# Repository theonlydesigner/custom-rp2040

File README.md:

# week 1: rp2040 dev board

## project goals
* **Target Specs:** custom RP2040 microcontroller board using the QFN-56 package, 16MB QSPI flash, 12MHz crystal oscillator, USB-C connector with 5.1k CC pull-down resistors and dual-row breakout headers for all GPIO pins to drive a mini hackpad.
* **Design Philosophy:** build a functional dev board from absolute ground zero using the hack club stasis guide so i finally understand what goes on under the hood of a raspberry pi pico [instead of treating microcontrollers like magic black boxes].
* **Why I'm building this:** week 1 theme is PCB and i needed a custom board to integrate with an old mini hackpad design i had lying around. also i wanted to suffer through routing 0402 passives and tiny IC pins.

## deep brief
this project is essentially a custom raspberry pi pico clone built from scratch using the hack club stasis devboard guide. instead of buying a ready-made dev board you have to manually route every single trace and place every tiny passive component [because suffering builds character]. 

at the center of the madness is the RP2040 microcontroller chip which handles all the processing. it is paired with a W25Q128 QSPI flash memory chip for storing firmware and a 12MHz crystal oscillator to provide the clock signal. power is delivered via a USB-C connector featuring 5.1k pull-down resistors so modern power supplies actually negotiate power correctly. an MCP1700 LDO voltage regulator takes that input and steps it down to a stable 3.3V for the system. finally every single GPIO pin is broken out onto dual headers so the board can easily interface with a mini hackpad.

## bill of materials (BOM)

| Part | Quantity | No of items in 1 unit | Price w/o shipping | Price |
| :--- | :---: | :---: | :---: | :---: |
| 1uF Capacitor | 1 | 2 | 0.1 | 0.1 |
| 0.1uF Capacitor | 1 | 11 | 0.1 | 0.1 |
| 10uF Capacitor | 1 | 2 | 0.1 | 0.1 |
| 33pF Capacitor | 1 | 2 | 0.2 | 0.2 |
| USB_C_Receptacle_USB2.0_14P | 1 | 1 | 0.3 | 0.3 |
| Conn_01x20 | 1 | 2 | 0.6 | 0.6 |
| Conn_01x03 | 1 | 1 | 0.16 | 0.16 |
| 5.1K Resistor | 1 | 2 | 0.1 | 0.1 |
| 27 Resistor | 1 | 2 | 0.1 | 0.1 |
| 1K Resistor | 1 | 2 | 0.1 | 0.1 |
| 10K Resistor | 1 | 1 | 0.1 | 0.1 |
| SW_Push | 1 | 1 | 0.11 | 0.11 |
| RP2040 Chip | 1 | 1 | 0.84 | 1.3 |
| MCP1700x-330xxTT | 1 | 1 | 0.5 | 0.5 |
| W25Q128JVS | 1 | 1 | 5.02 | 5.02 |
| 12MHz Crystal | 1 | 1 | 0.39 | 0.39 |
| PCB w/ Stencil | 1 | 1 | 6 | 10 |
| Solder Paste | 1 | 1 | 2.3 | 3 |
| Tweezers | 1 | 1 | 1.8 | 1.8 |
| Solder Iron and stuff related to that | 1 | 1 | 3.2 | 3.2 |

## visual showcase

*(a gorgeous 3D render of a board that will probably release the magic smoke the second power is applied)*

*(the schematic page where i stared into the void until the net names started making sense)*

*(the actual PCB layout before sending it off to the fab house to be judged)*

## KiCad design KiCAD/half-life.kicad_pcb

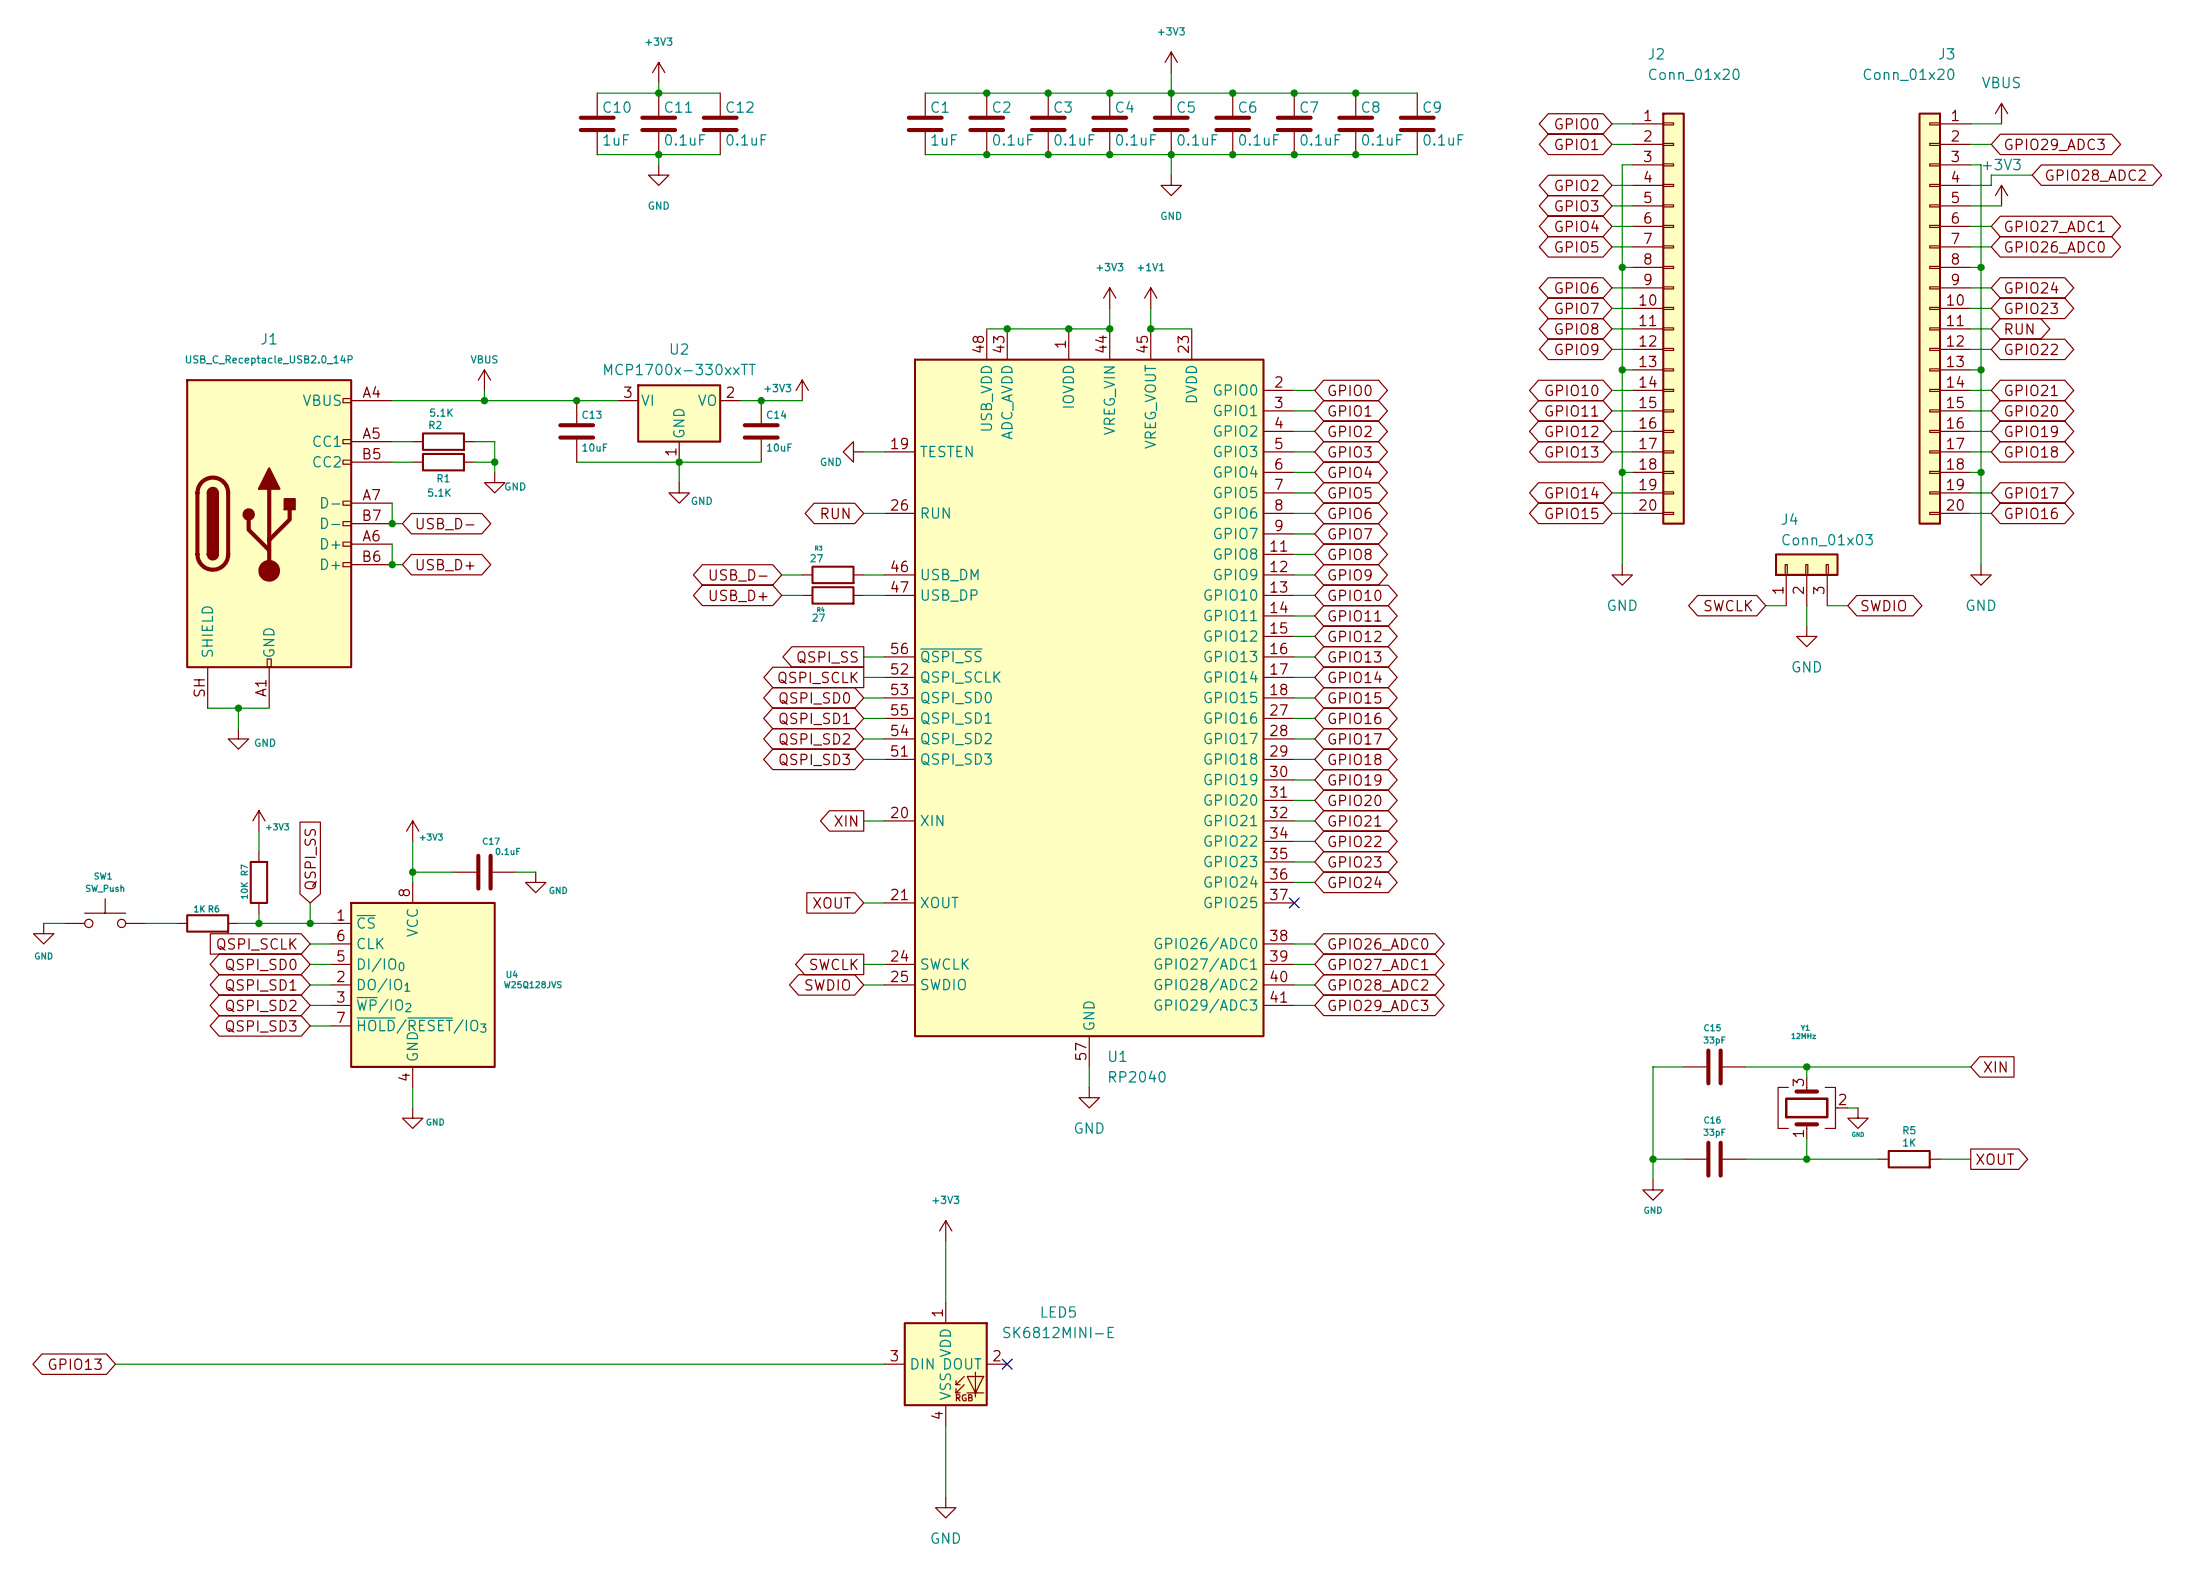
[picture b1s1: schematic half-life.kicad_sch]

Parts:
C1, C10: 1uF; C_0402_1005Metric
C2, C3, C4, C5, C6, C7, C8, C9, C11, C12, C17: 0.1uF; C_0402_1005Metric
C13, C14: 10uF; C_0603_1608Metric
C15, C16: 33pF; C_0603_1608Metric
J1: USB_C_Receptacle_USB2.0_14P; USB_C_Receptacle_HRO_TYPE-C-31-M-12
J2, J3: Conn_01x20; PinHeader_1x20_P2.54mm_Vertical
J4: Conn_01x03; PinHeader_1x03_P2.54mm_Vertical
LED5: SK6812MINI-E; LED_SK6812MINI-E_3.2x2.8mm_P1.5mm_ReverseMount
R1, R2: 5.1K; R_0402_1005Metric
R3, R4: 27; R_0402_1005Metric
R5, R6: 1K; R_0402_1005Metric
R7: 10K; R_0402_1005Metric
SW1: SW_Push; SW_Push_SPST_NO_Alps_SKRK
U1: RP2040; QFN-56-1EP_7x7mm_P0.4mm_EP3.2x3.2mm
U2: MCP1700x-330xxTT; SOT-23
U4: W25Q128JVS; Winbond_USON-8-1EP_3x2mm_P0.5mm_EP0.2x1.6mm
Y1: 12MHz; Crystal_SMD_3225-4Pin_3.2x2.5mm

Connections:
+1V1: U1.23 (DVDD), U1.45 (VREG_VOUT), U1.50 (DVDD)
+3V3: C1.1, C2.1, C3.1, C4.1, C5.1, C6.1, C7.1, C8.1, C9.1, C10.1, C11.1, C12.1, C14.1, C17.1, J3.5, LED5.1 (VDD), R7.2, U1.1 (IOVDD), U1.10 (IOVDD), U1.22 (IOVDD), U1.33 (IOVDD), U1.42 (IOVDD), U1.43 (ADC_AVDD), U1.44 (VREG_VIN), U1.48 (USB_VDD), U1.49 (IOVDD), U2.2 (VO), U4.8 (VCC)
GND: C1.2, C2.2, C3.2, C4.2, C5.2, C6.2, C7.2, C8.2, C9.2, C10.2, C11.2, C12.2, C13.2, C14.2, C15.1, C16.1, C17.2, J1.A1 (GND), J1.A12 (GND), J1.B1 (GND), J1.B12 (GND), J1.SH (SHIELD), J2.3, J2.8, J2.13, J2.18, J3.3, J3.8, J3.13, J3.18, J4.2, LED5.4 (VSS), R1.2, R2.2, SW1.1, U1.19 (TESTEN), U1.57 (GND), U2.1 (GND), U4.4 (GND), Y1.2 (G), Y1.4 (G)
GPIO0: J2.1, U1.2 (GPIO0)
GPIO1: J2.2, U1.3 (GPIO1)
GPIO2: J2.4, U1.4 (GPIO2)
GPIO3: J2.5, U1.5 (GPIO3)
GPIO4: J2.6, U1.6 (GPIO4)
GPIO5: J2.7, U1.7 (GPIO5)
GPIO6: J2.9, U1.8 (GPIO6)
GPIO7: J2.10, U1.9 (GPIO7)
GPIO8: J2.11, U1.11 (GPIO8)
GPIO9: J2.12, U1.12 (GPIO9)
GPIO10: J2.14, U1.13 (GPIO10)
GPIO11: J2.15, U1.14 (GPIO11)
GPIO12: J2.16, U1.15 (GPIO12)
GPIO13: J2.17, LED5.3 (DIN), U1.16 (GPIO13)
GPIO14: J2.19, U1.17 (GPIO14)
GPIO15: J2.20, U1.18 (GPIO15)
GPIO16: J3.20, U1.27 (GPIO16)
GPIO17: J3.19, U1.28 (GPIO17)
GPIO18: J3.17, U1.29 (GPIO18)
GPIO19: J3.16, U1.30 (GPIO19)
GPIO20: J3.15, U1.31 (GPIO20)
GPIO21: J3.14, U1.32 (GPIO21)
GPIO22: J3.12, U1.34 (GPIO22)
GPIO23: J3.10, U1.35 (GPIO23)
GPIO24: J3.9, U1.36 (GPIO24)
GPIO26_ADC0: J3.7, U1.38 (GPIO26/ADC0)
GPIO27_ADC1: J3.6, U1.39 (GPIO27/ADC1)
GPIO28_ADC2: J3.4, U1.40 (GPIO28/ADC2)
GPIO29_ADC3: J3.2, U1.41 (GPIO29/ADC3)
unnamed: C16.2, R5.1, Y1.1
unnamed: J1.A5 (CC1), R2.1
unnamed: J1.B5 (CC2), R1.1
unnamed: R6.1, SW1.2
unnamed: R3.2, U1.46 (USB_DM)
unnamed: R4.2, U1.47 (USB_DP)
QSPI_SCLK: U1.52 (QSPI_SCLK), U4.6 (CLK)
QSPI_SD0: U1.53 (QSPI_SD0), U4.5 (DI/IO_{0})
QSPI_SD1: U1.55 (QSPI_SD1), U4.2 (DO/IO_{1})
QSPI_SD2: U1.54 (QSPI_SD2), U4.3 (~WP/IO_{2})
QSPI_SD3: U1.51 (QSPI_SD3), U4.7 (~HOLD/~RESET/IO_{3})
QSPI_SS: R6.2, R7.1, U1.56 (~QSPI_SS), U4.1 (~CS)
RUN: J3.11, U1.26 (RUN)
SWCLK: J4.1, U1.24 (SWCLK)
SWDIO: J4.3, U1.25 (SWDIO)
USB_D+: J1.A6 (D+), J1.B6 (D+), R4.1
USB_D-: J1.A7 (D-), J1.B7 (D-), R3.1
VBUS: C13.1, J1.A4 (VBUS), J1.A9 (VBUS), J1.B4 (VBUS), J1.B9 (VBUS), J3.1, U2.3 (VI)
XIN: C15.2, U1.20 (XIN), Y1.3
XOUT: R5.2, U1.21 (XOUT)

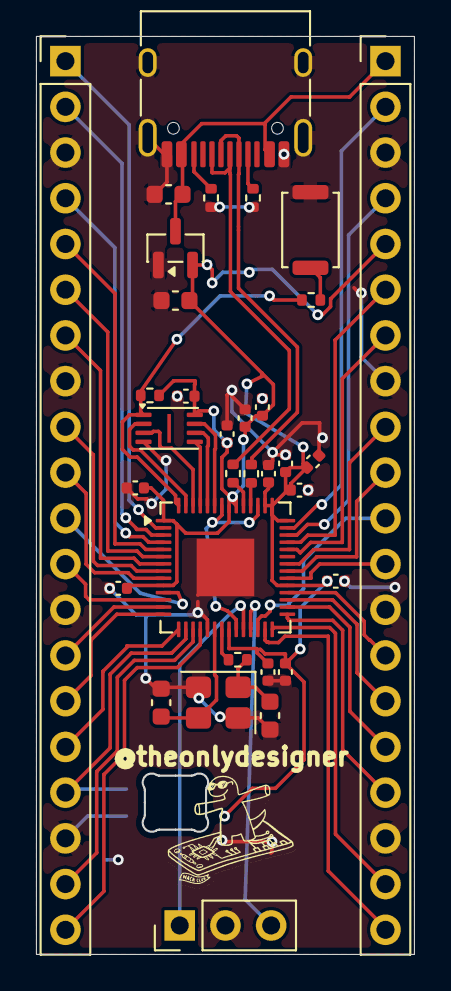
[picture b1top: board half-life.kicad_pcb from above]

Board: 2 copper layers, 21.0 x 51.0 mm, 34 parts (1 on the bottom side), 52 nets.

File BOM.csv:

Item,Qty,Supplier,Cost/item,Total Cost,link
1uF Capacitor,1,,$0.10,$0.10,
0.1uF Capacitor,1,,$0.10,$0.10,
10uF Capacitor,1,,$0.10,$0.10,
33pF Capacitor,1,,$0.20,$0.20,
USB_C_Receptacle_USB2.0_14P,1,,$0.30,$0.30,
Conn_01x20,1,,$0.60,$0.60,
Conn_01x03,1,,$0.16,$0.16,
5.1K Resistor,1,,$0.10,$0.10,
27 Resistor,1,,$0.10,$0.10,
1K Resistor,1,,$0.10,$0.10,
10K Resistor,1,,$0.10,$0.10,
SW_Push,1,,$0.11,$0.11,
RP2040 Chip,1,,$1.30,$1.30,
MCP1700x-330xxTT,1,,$0.50,$0.50,
W25Q128JVS,1,,$5.02,$5.02,
12MHz Crystal,1,,$0.39,$0.39,
PCB w/ Stencil,1,,$10.00,$10.00,
Solder Paste,1,,$3.00,$3.00,
Estimated total shipping,1,,,$0.00,
